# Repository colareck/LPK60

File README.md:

This is a 60% keyboard designed to use kailh choc switches. It has a full size 6.25u space bar.

## Keyboard design

The keyboard is designed to use QMK firmware (still working on my commit for the QMK repo) with an STM32F072CBT6 microcontroller. The board should accept both v1 and v2 choc switches, it is importnat to note that with the current version the esc, tab, 1, and Q keys will need the plastic posts trimmed if using v1 switches. This was a design flaw that will be corrected in the next verison. MBK keycaps fit well, but I have not tested other keycaps. Currently, the only place I have sourced the 6.25u spacebar is from a custom order at fkcaps.com.

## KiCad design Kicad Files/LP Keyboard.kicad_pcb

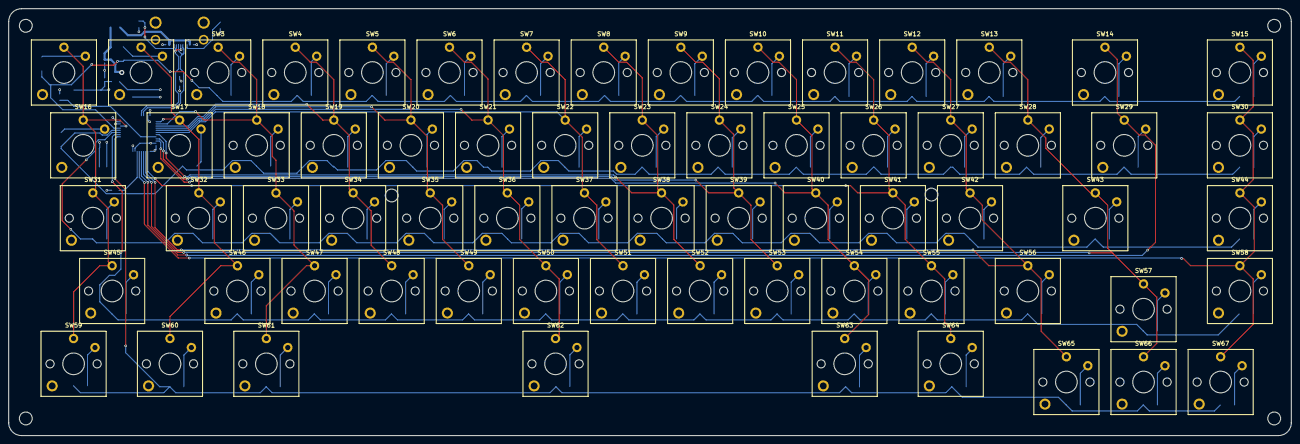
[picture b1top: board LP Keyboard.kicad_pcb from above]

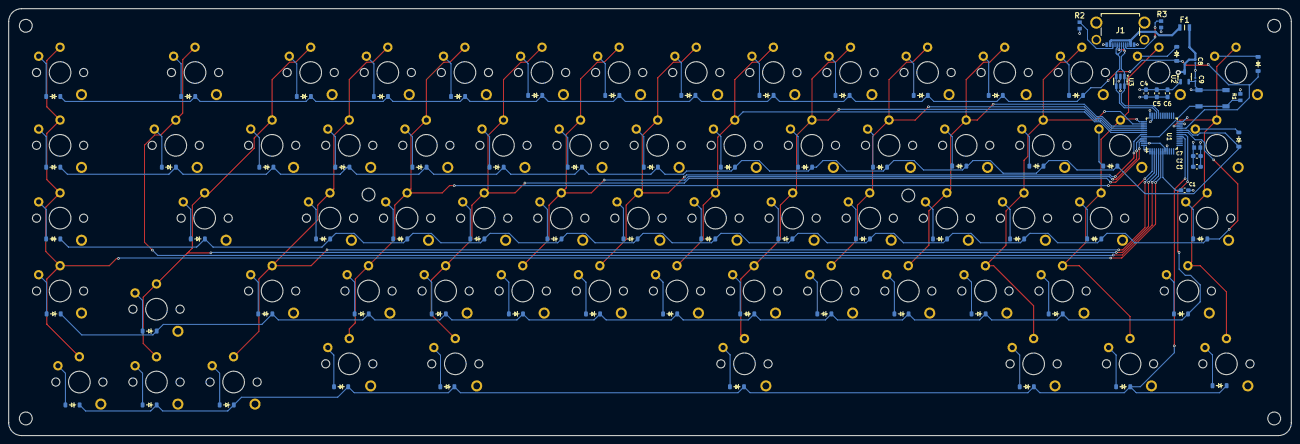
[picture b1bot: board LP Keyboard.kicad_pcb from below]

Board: 4 copper layers, 299.4 x 99.7 mm, 152 parts (85 on the bottom side), 97 nets.

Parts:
C1, C2, C3, C4, C5, C6: 100nF; C_0603_1608Metric_Pad1.08x0.95mm_HandSolder
C7: 10uF; 10uF Cap CAPC1608X100N
C8, C9: 1uF; 1uF lil CAPC0603X33N
D1, D2, D3, D4, D5, D6, D7, D8, D9, D10, D11, D12, D13, D14, D15, D16, D17, D18, D19, D20, D21, D22, D23, D24, D25, D26, D27, D28, D29, D30, D31, D32, D33, D34, D35, D36, D37, D38, D39, D40, D41, D42, D43, D44, D45, D46, D47, D48, D49, D50, D51, D52, D53, D54, D55, D56, D57, D58, D59, D60, D61, D62, D63, D64, D65, D66, D67: D_Small; Diode_SOD-123
F1: 500mA PPTC; FUSC2214X80N
J1: USB4500-03-0-A; USB4500030A
R1: 10k; RESC1608X50N
R2, R3: 5.1k; RESC1608X50N
SW1, SW2: SW_Push; Choc_V2_1.00u
SW3, SW4, SW5, SW6, SW7, SW8, SW9, SW10, SW11, SW12, SW13, SW15, SW18, SW19, SW20, SW21, SW22, SW23, SW24, SW25, SW26, SW27, SW28, SW30, SW32, SW33, SW34, SW35, SW36, SW37, SW38, SW39, SW40, SW41, SW42, SW44, SW46, SW47, SW48, SW49, SW50, SW51, SW52, SW53, SW54, SW55, SW57, SW58, SW65, SW66, SW67: SW_Push; Choc_V1V2_1.00u
SW14: SW_Push; Choc_V1V2_2.00u
SW16, SW17: SW_Push; Choc_V2_1.50u
SW29, SW56, SW64: SW_Push; Choc_V1V2_1.50u
SW31: SW_Push; Choc_V1V2_1.75u
SW43, SW45: SW_Push; Choc_V1V2_2.25u
SW59, SW60, SW61, SW63: SW_Push; Choc_V1V2_1.25u
SW62: SW_Push; Choc_V1V2_6.25u
SW68: Boot Button; Button_TL3342
U1: STM32F072CBT6; LQFP-48_7x7mm_P0.5mm
U2: XC6206P332MR-G; SOT-23-3
U3: USBLC6-2SC6; SOT-23-6

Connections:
+3V3: C2.1, C3.1, C4.1, C5.1, C6.1, C7.1, C9.1, SW68.2, U1.1 (VBAT), U1.9 (VDDA), U1.24 (VDD), U1.36 (VDDIO2), U1.48 (VDD), U2.2 (VO)
+5V: C8.1, F1.2, U2.3 (VI), U3.5 (VBUS)
D+: J1.A6 (DP1), J1.B6 (DP2), U1.33 (PA12), U3.3 (I/O2), U3.4 (I/O2)
D-: J1.A7 (DN1), J1.B7 (DN2), U1.32 (PA11), U3.1 (I/O1), U3.6 (I/O1)
GND: C1.2, C2.2, C3.2, C4.2, C5.2, C6.2, C7.2, C8.2, C9.2, J1.A1 (GND_1), J1.A12 (GND_2), R1.2, R2.2, R3.1, U1.8 (VSSA), U1.23 (VSS), U1.35 (VSS), U1.47 (VSS), U2.1 (GND), U3.2 (GND)
unnamed: D1.2 (A), SW1.2
unnamed: D2.2 (A), SW2.2
unnamed: D3.2 (A), SW3.2
unnamed: D4.2 (A), SW4.2
unnamed: D5.2 (A), SW5.2
unnamed: D6.2 (A), SW6.2
unnamed: D7.2 (A), SW7.2
unnamed: D8.2 (A), SW8.2
unnamed: D9.2 (A), SW9.2
unnamed: D10.2 (A), SW10.2
unnamed: D11.2 (A), SW11.2
unnamed: D12.2 (A), SW12.2
unnamed: D13.2 (A), SW13.2
unnamed: D14.2 (A), SW14.2
unnamed: D15.2 (A), SW15.2
unnamed: D16.2 (A), SW16.2
unnamed: D17.2 (A), SW17.2
unnamed: D18.2 (A), SW18.2
unnamed: D19.2 (A), SW19.2
unnamed: D20.2 (A), SW20.2
unnamed: D21.2 (A), SW21.2
unnamed: D22.2 (A), SW22.2
unnamed: D23.2 (A), SW23.2
unnamed: D24.2 (A), SW24.2
unnamed: D25.2 (A), SW25.2
unnamed: D26.2 (A), SW26.2
unnamed: D27.2 (A), SW27.2
unnamed: D28.2 (A), SW28.2
unnamed: D29.2 (A), SW29.2
unnamed: D30.2 (A), SW30.2
unnamed: D31.2 (A), SW31.2
unnamed: D32.2 (A), SW32.2
unnamed: D33.2 (A), SW33.2
unnamed: D34.2 (A), SW34.2
unnamed: D35.2 (A), SW35.2
unnamed: D36.2 (A), SW36.2
unnamed: D37.2 (A), SW37.2
unnamed: D38.2 (A), SW38.2
unnamed: D39.2 (A), SW39.2
unnamed: D40.2 (A), SW40.2
unnamed: D41.2 (A), SW41.2
unnamed: D42.2 (A), SW42.2
unnamed: D43.2 (A), SW43.2
unnamed: D44.2 (A), SW44.2
unnamed: D45.2 (A), SW45.2
unnamed: D46.2 (A), SW46.2
unnamed: D47.2 (A), SW47.2
unnamed: D48.2 (A), SW48.2
unnamed: D49.2 (A), SW49.2
unnamed: D50.2 (A), SW50.2
unnamed: D51.2 (A), SW51.2
unnamed: D52.2 (A), SW52.2
unnamed: D53.2 (A), SW53.2
unnamed: D54.2 (A), SW54.2
unnamed: D55.2 (A), SW55.2
unnamed: D56.2 (A), SW56.2
unnamed: D57.2 (A), SW57.2
unnamed: D58.2 (A), SW58.2
unnamed: D59.2 (A), SW59.2
unnamed: D60.2 (A), SW60.2
unnamed: D61.2 (A), SW61.2
unnamed: D62.2 (A), SW62.2
unnamed: D63.2 (A), SW63.2
unnamed: D64.2 (A), SW64.2
unnamed: D65.2 (A), SW65.2
unnamed: D66.2 (A), SW66.2
unnamed: D67.2 (A), SW67.2
unnamed: J1.A5 (CC1), R3.2
unnamed: J1.B5 (CC2), R2.1
unnamed: R1.1, SW68.1, U1.44 (BOOT0)
unnamed: C1.1, U1.7 (NRST)
VBUS: F1.1, J1.A4 (VBUS_1), J1.A9 (VBUS_2)
col 0: SW1.1, SW16.1, SW31.1, SW45.1, SW59.1, U1.22 (PB11)
col 1: SW2.1, SW17.1, SW32.1, SW46.1, SW60.1, U1.37 (PA14)
col 2: SW3.1, SW18.1, SW33.1, SW47.1, SW61.1, U1.38 (PA15)
col 3: SW4.1, SW19.1, SW34.1, SW48.1, U1.39 (PB3)
col 4: SW5.1, SW20.1, SW35.1, SW49.1, U1.40 (PB4)
col 5: SW6.1, SW21.1, SW36.1, SW50.1, SW62.1, U1.41 (PB5)
col 6: SW7.1, SW22.1, SW37.1, SW51.1, U1.42 (PB6)
col 7: SW8.1, SW23.1, SW38.1, SW52.1, U1.43 (PB7)
col 8: SW9.1, SW24.1, SW39.1, SW53.1, U1.45 (PB8)
col 9: SW10.1, SW25.1, SW40.1, SW54.1, SW63.1, U1.46 (PB9)
col 10: SW11.1, SW26.1, SW41.1, SW55.1, SW64.1, U1.2 (PC13)
col 11: SW12.1, SW27.1, SW42.1, SW56.1, SW65.1, U1.3 (PC14)
col 12: SW13.1, SW28.1, SW43.1, SW57.1, SW66.1, U1.4 (PC15)
col 13: SW14.1, SW29.1, U1.5 (PF0)
col 14: SW15.1, SW30.1, SW44.1, SW58.1, SW67.1, U1.6 (PF1)
row 0: D1.1 (K), D2.1 (K), D3.1 (K), D4.1 (K), D5.1 (K), D6.1 (K), D7.1 (K), D8.1 (K), D9.1 (K), D10.1 (K), D11.1 (K), D12.1 (K), D13.1 (K), D14.1 (K), D15.1 (K), U1.21 (PB10)
row 1: D16.1 (K), D17.1 (K), D18.1 (K), D19.1 (K), D20.1 (K), D21.1 (K), D22.1 (K), D23.1 (K), D24.1 (K), D25.1 (K), D26.1 (K), D27.1 (K), D28.1 (K), D29.1 (K), D30.1 (K), U1.20 (PB2)
row 2: D31.1 (K), D32.1 (K), D33.1 (K), D34.1 (K), D35.1 (K), D36.1 (K), D37.1 (K), D38.1 (K), D39.1 (K), D40.1 (K), D41.1 (K), D42.1 (K), D43.1 (K), D44.1 (K), U1.19 (PB1)
row 3: D45.1 (K), D46.1 (K), D47.1 (K), D48.1 (K), D49.1 (K), D50.1 (K), D51.1 (K), D52.1 (K), D53.1 (K), D54.1 (K), D55.1 (K), D56.1 (K), D57.1 (K), D58.1 (K), U1.18 (PB0)
row 4: D59.1 (K), D60.1 (K), D61.1 (K), D62.1 (K), D63.1 (K), D64.1 (K), D65.1 (K), D66.1 (K), D67.1 (K), U1.17 (PA7)

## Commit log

2026-01-12 Added design files
    Added KLE json and png outputs. Added plate svg generated by plate.keeb.io.
2026-01-12 Create Kicad folder
2026-01-13 Corrected switch plate SVG
2026-01-13 Delete kbplate(3).svg
    old switch plate svg, doesn't work
